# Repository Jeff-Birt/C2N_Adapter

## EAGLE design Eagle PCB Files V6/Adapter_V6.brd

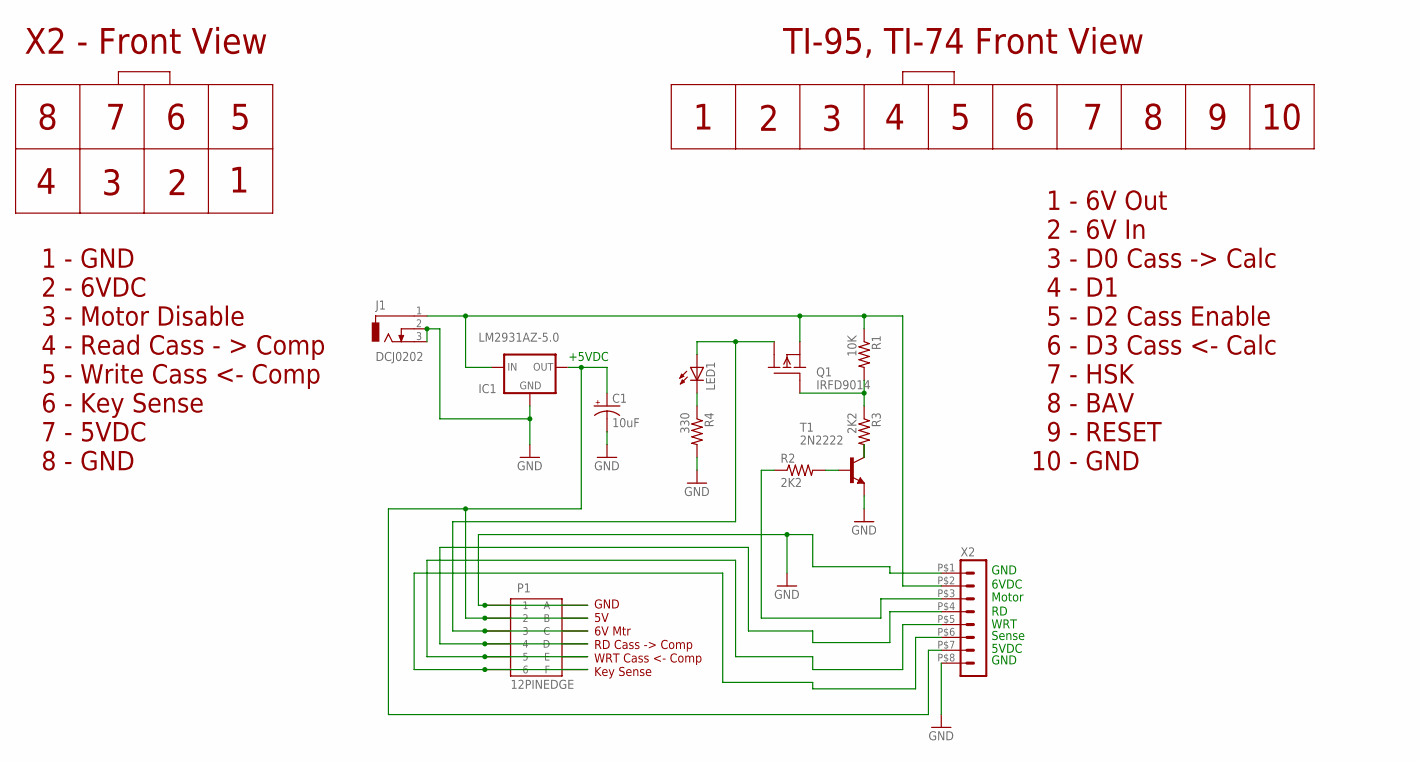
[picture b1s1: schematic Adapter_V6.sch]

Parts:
C1: 10uF; E1,8-4
IC1: LM2931AZ-5.0; TO92
J1: DCJ0202
LED1: LED5MM
P1: 12PINEDGE
Q1: IRFD9014; DIL04
R1: 10K; 0207/10
R2, R3: 2K2; 0207/10
R4: 330; 0207/10
T1: 2N2222; TO18
X2: HEADER_POS8_43045-0800; 43045-0800

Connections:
GND: C1.-, IC1.2 (GND), J1.2, J1.3, P1.1, P1.A, R4.2, T1.1 (E), X2.P$1 (1), X2.P$8 (8)
unnamed: IC1.3 (IN), J1.1, Q1.2 (S), R1.1, X2.P$2 (2)
unnamed: C1.+, IC1.1 (OUT), P1.2, P1.B, X2.P$7 (7)
unnamed: R2.1, X2.P$3 (3)
unnamed: P1.4, P1.D, X2.P$4 (4)
unnamed: P1.5, P1.E, X2.P$5 (5)
unnamed: P1.6, P1.F, X2.P$6 (6)
unnamed: R2.2, T1.2 (B)
unnamed: LED1.A, P1.3, P1.C, Q1.3 (D1)
unnamed: R3.2, T1.3 (C)
unnamed: Q1.1 (G), R1.2, R3.1
unnamed: LED1.K (C), R4.1

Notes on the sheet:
GND
+5VDC
Motor
WRT
Sense
6VDC
5VDC
X2 - Front View
1 - GND 2 - 6VDC 3 - Motor Disable 4 - Read Cass - > Comp 5 - Write Cass <- Comp 6 - Key Sense 7 - 5VDC 8 - GND
1 - 6V Out 2 - 6V In 3 - D0 Cass -> Calc 4 - D1 5 - D2 Cass Enable 6 - D3 Cass <- Calc 7 - HSK 8 - BAV 9 - RESET 10 - GND
TI-95, TI-74 Front View
GND 5V 6V Mtr RD Cass -> Comp WRT Cass <- Comp Key Sense

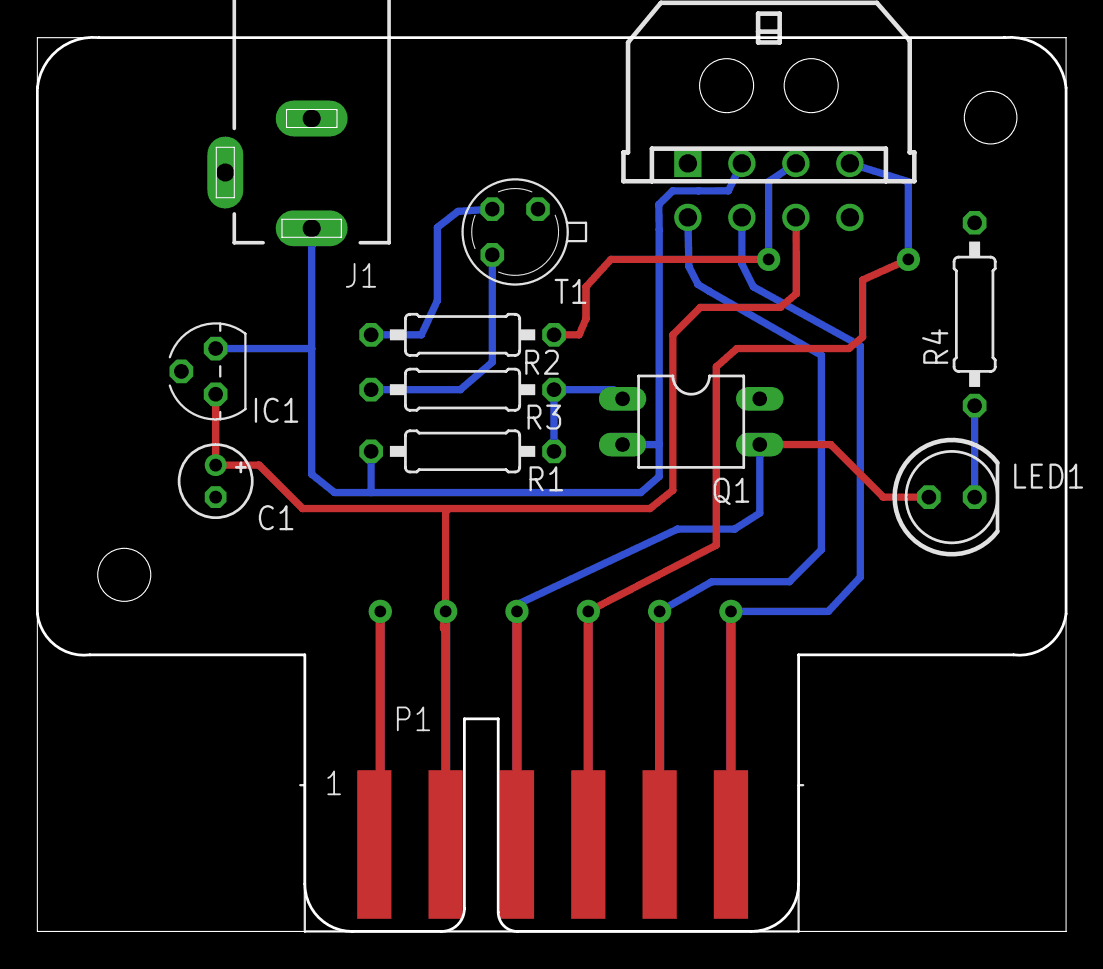
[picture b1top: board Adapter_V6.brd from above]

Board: 2 copper layers, 57.1 x 49.7 mm, 12 parts (0 on the bottom side), 12 nets.

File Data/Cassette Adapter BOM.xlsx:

Manufacturer | Part # | Qty | Description | Source | Price Ea. $ | Price Ext.
For adapter
AdaFruit | 373 | 1 | DC Power Jack, OD-5.5mm, ID-2.1mm | https://www.mouser.com/ProductDetail/485-373 | 0.95 | 0.95
Vishay | IRFD9014PBF | 1 | MOSFET Transistor, power switch | https://www.mouser.com/ProductDetail/844-IRFD9014PBF | 0.95 | 0.95
Molex | 43045-0800 | 1 | 2x4 Right Angle PCB count con. | https://www.mouser.com/ProductDetail/538-43045-0800 | 2.2000000000000002 | 2.2000000000000002
Molex | 538-43025-0800 | 1 | 2x4 Male connector housing | https://www.mouser.com/ProductDetail/538-43025-0800 | 0.52 | 0.52
Molex | 43030-0007 | 8 | Female crimp pins for above housing | https://www.mouser.com/ProductDetail/538-43030-0007 | 0.19 | 1.52
ON | LM2931AZ-5.0RPG | 1 | 5V Regulator, TO-92 case | https://www.mouser.com/ProductDetail/863-LM2931AZ-5.0RPG | 0.59 | 0.59
Misc | 2N222A | 1 | NPN Transistor | https://www.bgmicro.com/TRN2N2222AMetal.aspx | 0.27 | 0.27
Misc |  | 2 | 2.2K 1/4W resistor |  | 0.1 | 0.2
Misc |  | 1 | 10K 1/4W resistor |  | 0.1 | 0.1
Misc |  | 1 | 330ohm 1/4W resistor |  | 0.1 | 0.1
Misc |  | 1 | T1-3/4 LED |  | 0.1 | 0.1
Misc |  | 1 | 10uF 16V electrolytic capacitor |  | 0.1 | 0.1
For TI-94/74
Amphenol | 78211-010LF | 1 | 0.1" 1x10 Female housing | https://www.mouser.com/ProductDetail/649-78211-010LF | 1.28 | 1.28
Amphenol | 47715-000LF | 10 | Female crimp pins for above houing | https://www.mouser.com/ProductDetail/649-47715-000LF | 0.42 | 4.2
 |  |  |  | Total |  | 13.079999999999998

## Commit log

2018-11-23 Add files via upload
    Initial commit

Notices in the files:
parts and their libraries:
SparkFun-Aesthetics: Licensing: CC v3.0 Share-Alike You are welcome to use this library for commercial purposes.
